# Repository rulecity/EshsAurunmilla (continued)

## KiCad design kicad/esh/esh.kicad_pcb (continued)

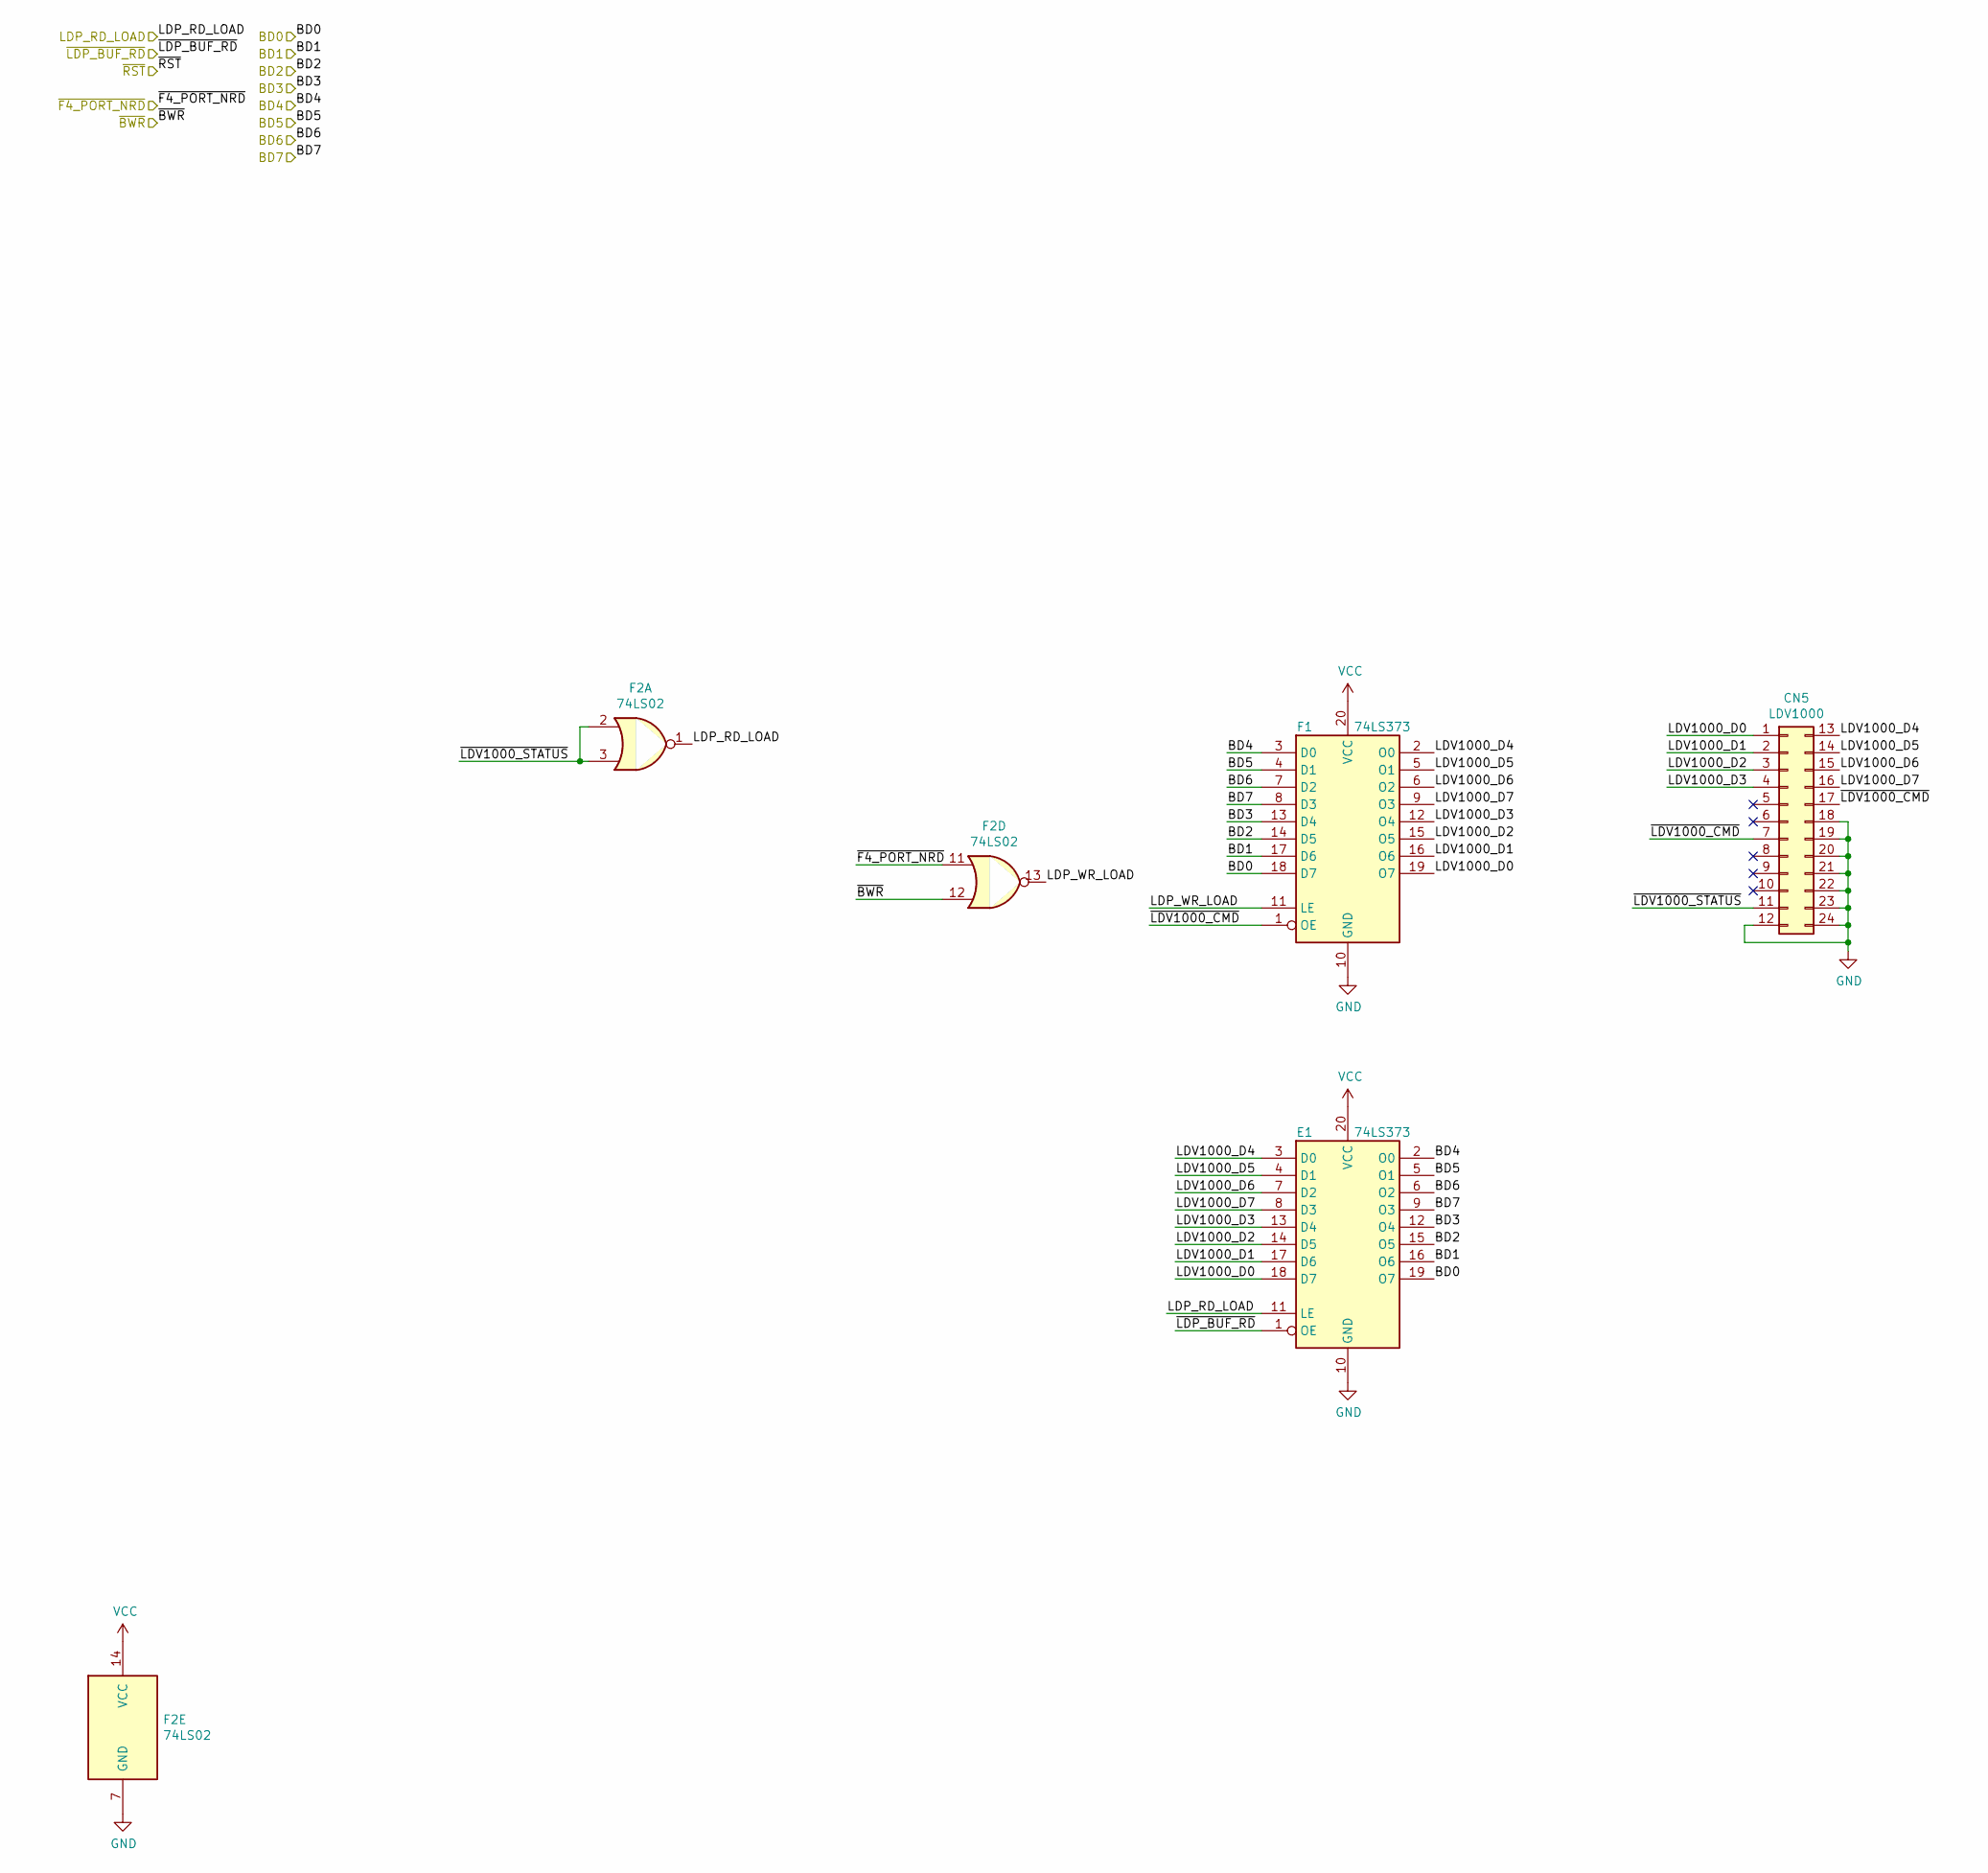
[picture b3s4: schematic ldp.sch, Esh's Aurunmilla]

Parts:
CN5: LDV1000; Esh_LDV1000
E1: 74LS373; DIP-20_W7.62mm_Socket
F1: 74LS373; DIP-20_W7.62mm_Socket
F2: 74LS02; DIP-14_W7.62mm_Socket

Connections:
/BD0: E1.19 (O7), F1.18 (D7); also elsewhere on the board
/BD1: E1.16 (O6), F1.17 (D6); also elsewhere on the board
/BD2: E1.15 (O5), F1.14 (D5); also elsewhere on the board
/BD3: E1.12 (O4), F1.13 (D4); also elsewhere on the board
/BD4: E1.2 (O0), F1.3 (D0); also elsewhere on the board
/BD5: E1.5 (O1), F1.4 (D1); also elsewhere on the board
/BD6: E1.6 (O2), F1.7 (D2); also elsewhere on the board
/BD7: E1.9 (O3), F1.8 (D3); also elsewhere on the board
/LDP_RD_LOAD: E1.11 (LE), F2.1; also elsewhere on the board
/ldp/LDP_WR_LOAD: F1.11 (LE), F2.13
/ldp/LDV1000_D0: CN5.1, E1.18 (D7), F1.19 (O7)
/ldp/LDV1000_D1: CN5.2, E1.17 (D6), F1.16 (O6)
/ldp/LDV1000_D2: CN5.3, E1.14 (D5), F1.15 (O5)
/ldp/LDV1000_D3: CN5.4, E1.13 (D4), F1.12 (O4)
/ldp/LDV1000_D4: CN5.13, E1.3 (D0), F1.2 (O0)
/ldp/LDV1000_D5: CN5.14, E1.4 (D1), F1.5 (O1)
/ldp/LDV1000_D6: CN5.15, E1.7 (D2), F1.6 (O2)
/ldp/LDV1000_D7: CN5.16, E1.8 (D3), F1.9 (O3)
/ldp/~LDV1000_CMD: CN5.7, CN5.17, F1.1 (OE)
/ldp/~LDV1000_STATUS: CN5.11, F2.2, F2.3
/~BWR: F2.12; also elsewhere on the board
/~F4_PORT_NRD: F2.11; also elsewhere on the board
/~LDP_BUF_RD: E1.1 (OE); also elsewhere on the board
GND: CN5.12, CN5.18, CN5.19, CN5.20, CN5.21, CN5.22, CN5.23, CN5.24, E1.10 (GND), F1.10 (GND), F2.7 (GND); also elsewhere on the board
VCC: E1.20 (VCC), F1.20 (VCC), F2.14 (VCC); also elsewhere on the board

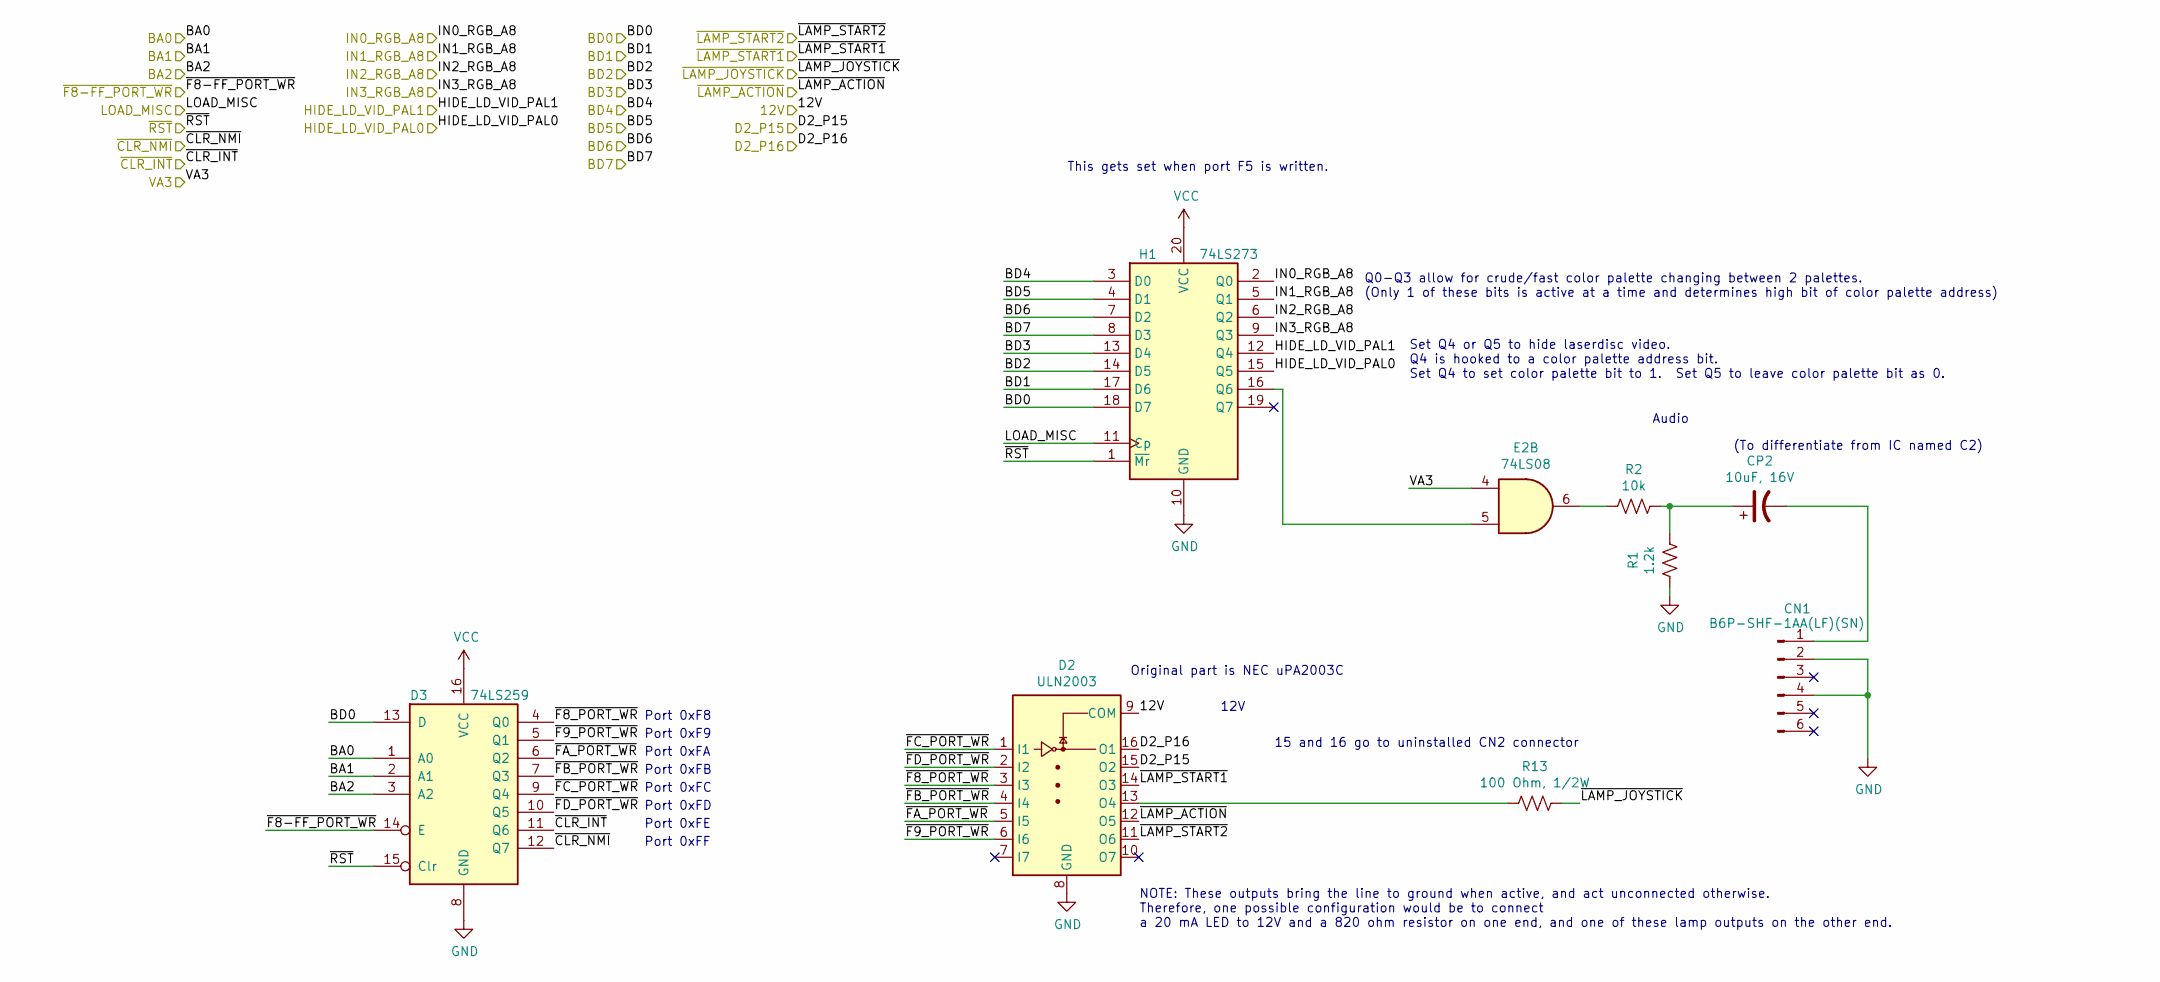
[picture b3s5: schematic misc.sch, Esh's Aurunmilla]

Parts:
CN1: B6P-SHF-1AA(LF)(SN); PinHeader_1x06_P2.54mm_Vertical
CP2: 10uF, 16V; CP_Radial_D5.0mm_P2.50mm
D2: ULN2003; DIP-16_W7.62mm_Socket
D3: 74LS259; DIP-16_W7.62mm_Socket
E2: 74LS08; DIP-14_W7.62mm_Socket
H1: 74LS273; DIP-20_W7.62mm_Socket
R1: 1.2k; R_Axial_DIN0207_L6.3mm_D2.5mm_P10.16mm_Horizontal
R2: 10k; R_Axial_DIN0207_L6.3mm_D2.5mm_P10.16mm_Horizontal
R13: 100 Ohm, 1/2W; R_Axial_DIN0207_L6.3mm_D2.5mm_P10.16mm_Horizontal

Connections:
/12V: D2.9 (COM); also elsewhere on the board
/BA0: D3.1 (A0); also elsewhere on the board
/BA1: D3.2 (A1); also elsewhere on the board
/BA2: D3.3 (A2); also elsewhere on the board
/BD0: D3.13 (D), H1.18 (D7); also elsewhere on the board
/BD1: H1.17 (D6); also elsewhere on the board
/BD2: H1.14 (D5); also elsewhere on the board
/BD3: H1.13 (D4); also elsewhere on the board
/BD4: H1.3 (D0); also elsewhere on the board
/BD5: H1.4 (D1); also elsewhere on the board
/BD6: H1.7 (D2); also elsewhere on the board
/BD7: H1.8 (D3); also elsewhere on the board
/D2_P15: D2.15 (O2); also elsewhere on the board
/D2_P16: D2.16 (O1); also elsewhere on the board
/HIDE_LD_VID_PAL0: H1.15 (Q5); also elsewhere on the board
/HIDE_LD_VID_PAL1: H1.12 (Q4); also elsewhere on the board
/IN0_RGB_A8: H1.2 (Q0); also elsewhere on the board
/IN1_RGB_A8: H1.5 (Q1); also elsewhere on the board
/IN2_RGB_A8: H1.6 (Q2); also elsewhere on the board
/IN3_RGB_A8: H1.9 (Q3); also elsewhere on the board
/LOAD_MISC: H1.11 (Cp); also elsewhere on the board
/VA3: E2.4; also elsewhere on the board
/misc/~F8_PORT_WR: D2.3 (I3), D3.4 (Q0)
/misc/~F9_PORT_WR: D2.6 (I6), D3.5 (Q1)
/misc/~FA_PORT_WR: D2.5 (I5), D3.6 (Q2)
/misc/~FB_PORT_WR: D2.4 (I4), D3.7 (Q3)
/misc/~FC_PORT_WR: D2.1 (I1), D3.9 (Q4)
/misc/~FD_PORT_WR: D2.2 (I2), D3.10 (Q5)
/~CLR_INT: D3.11 (Q6); also elsewhere on the board
/~CLR_NMI: D3.12 (Q7); also elsewhere on the board
/~F8-FF_PORT_WR: D3.14 (E); also elsewhere on the board
/~LAMP_ACTION: D2.12 (O5); also elsewhere on the board
/~LAMP_JOYSTICK: R13.1; also elsewhere on the board
/~LAMP_START1: D2.14 (O3); also elsewhere on the board
/~LAMP_START2: D2.11 (O6); also elsewhere on the board
/~RST: D3.15 (Clr), H1.1 (~Mr); also elsewhere on the board
GND: CN1.2, CN1.4, D2.8 (GND), D3.8 (GND), H1.10 (GND), R1.2; also elsewhere on the board
unnamed: CN1.1, CP2.2
unnamed: CP2.1, R1.1, R2.1
unnamed: D2.13 (O4), R13.2
unnamed: E2.5, H1.16 (Q6)
unnamed: E2.6, R2.2
VCC: D3.16 (VCC), H1.20 (VCC); also elsewhere on the board

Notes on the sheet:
Port 0xFF
Port 0xFE
Port 0xF8
Port 0xF9
Port 0xFA
Port 0xFB
Port 0xFC
Port 0xFD
15 and 16 go to uninstalled CN2 connector
Original part is NEC uPA2003C
12V
This gets set when port F5 is written.
Audio
(To differentiate from IC named C2)
Set Q4 or Q5 to hide laserdisc video. Q4 is hooked to a color palette address bit. Set Q4 to set color palette bit to 1. Set Q5 to leave color palette bit as 0.
Q0-Q3 allow for crude/fast color palette changing between 2 palettes. (Only 1 of these bits is active at a time and determines high bit of color palette address)
NOTE: These outputs bring the line to ground when active, and act unconnected otherwise. Therefore, one possible configuration would be to connect a 20 mA LED to 12V and a 820 ohm resistor on one end, and one of these lamp outputs on the other end.

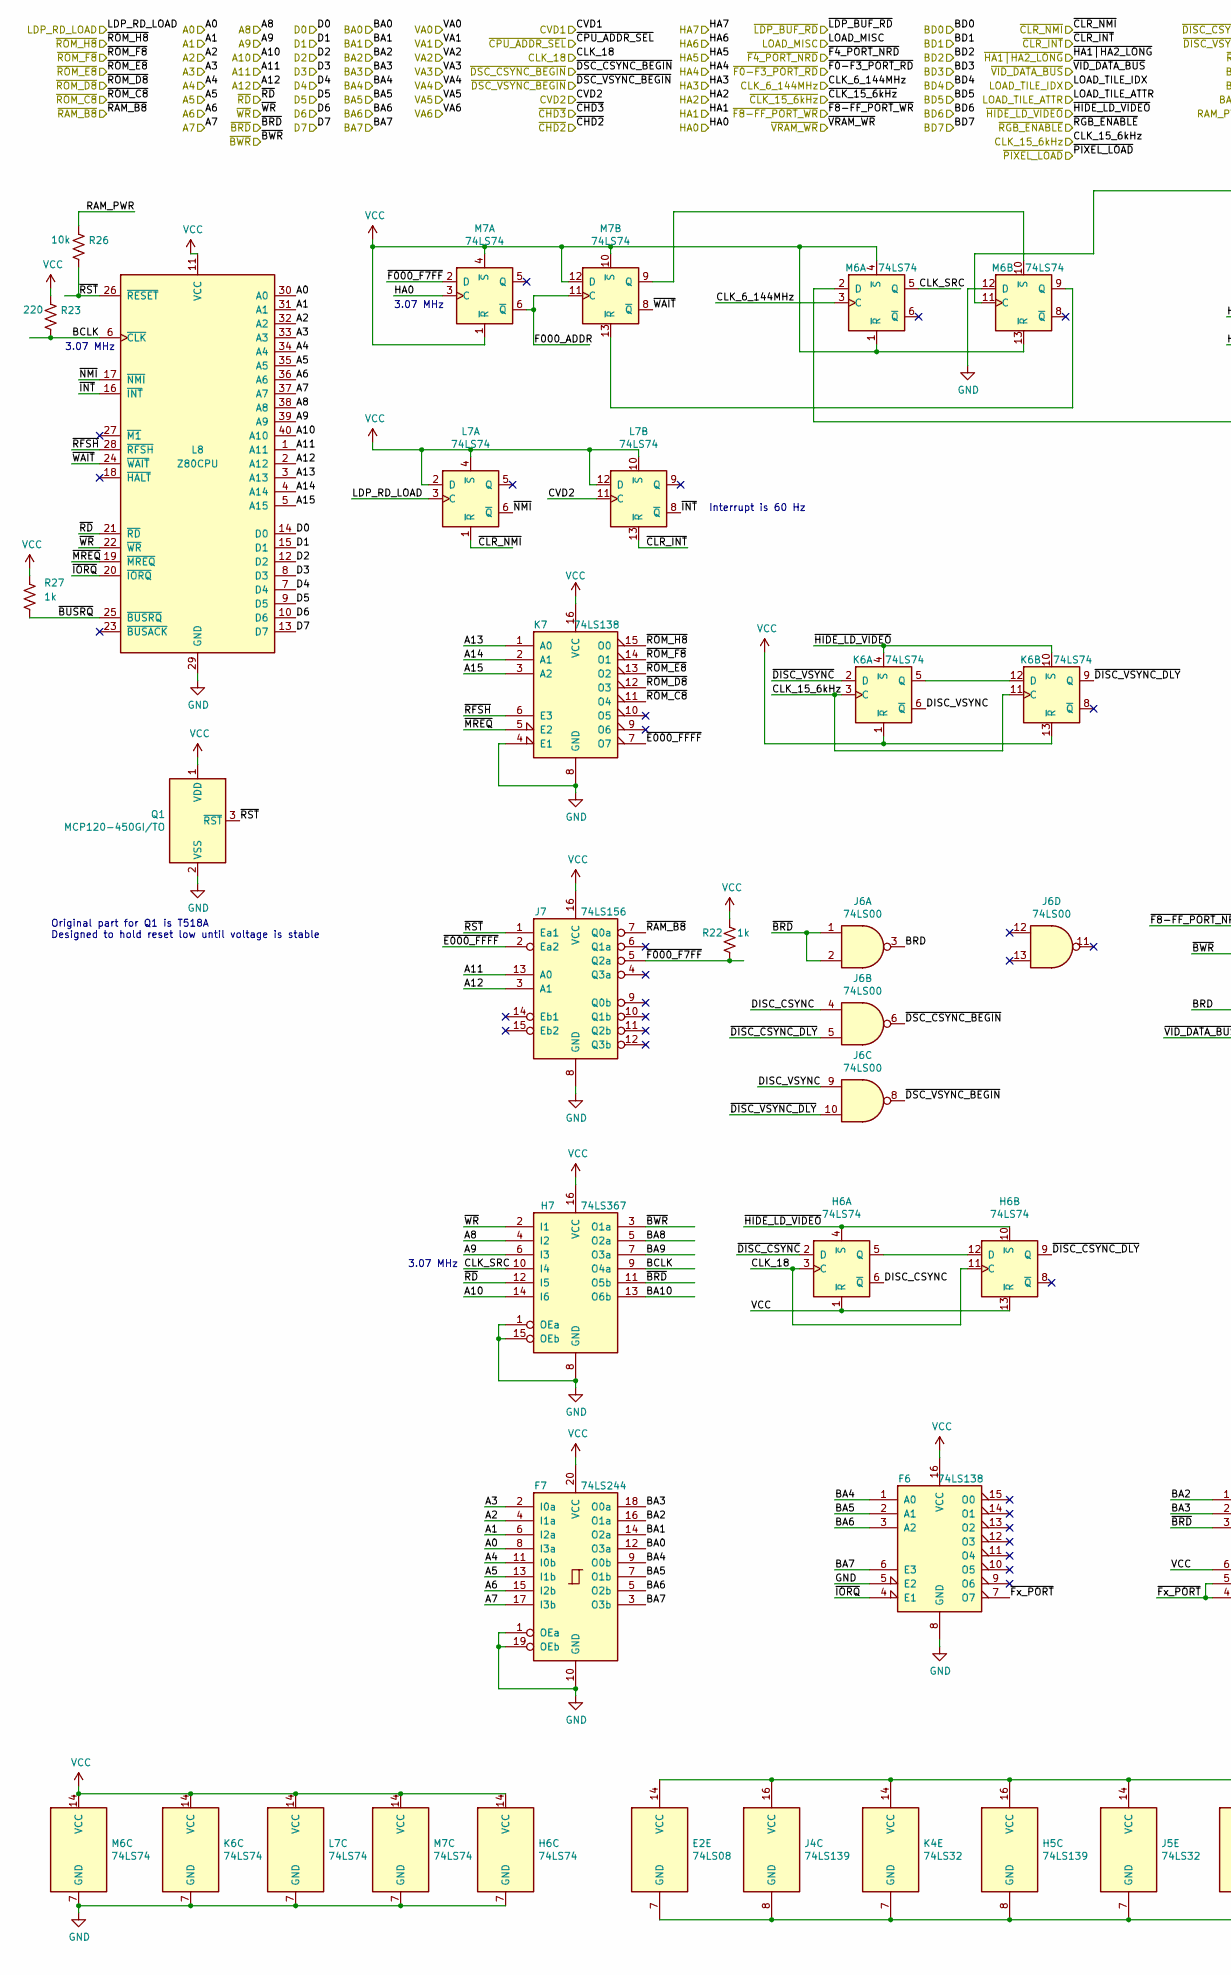
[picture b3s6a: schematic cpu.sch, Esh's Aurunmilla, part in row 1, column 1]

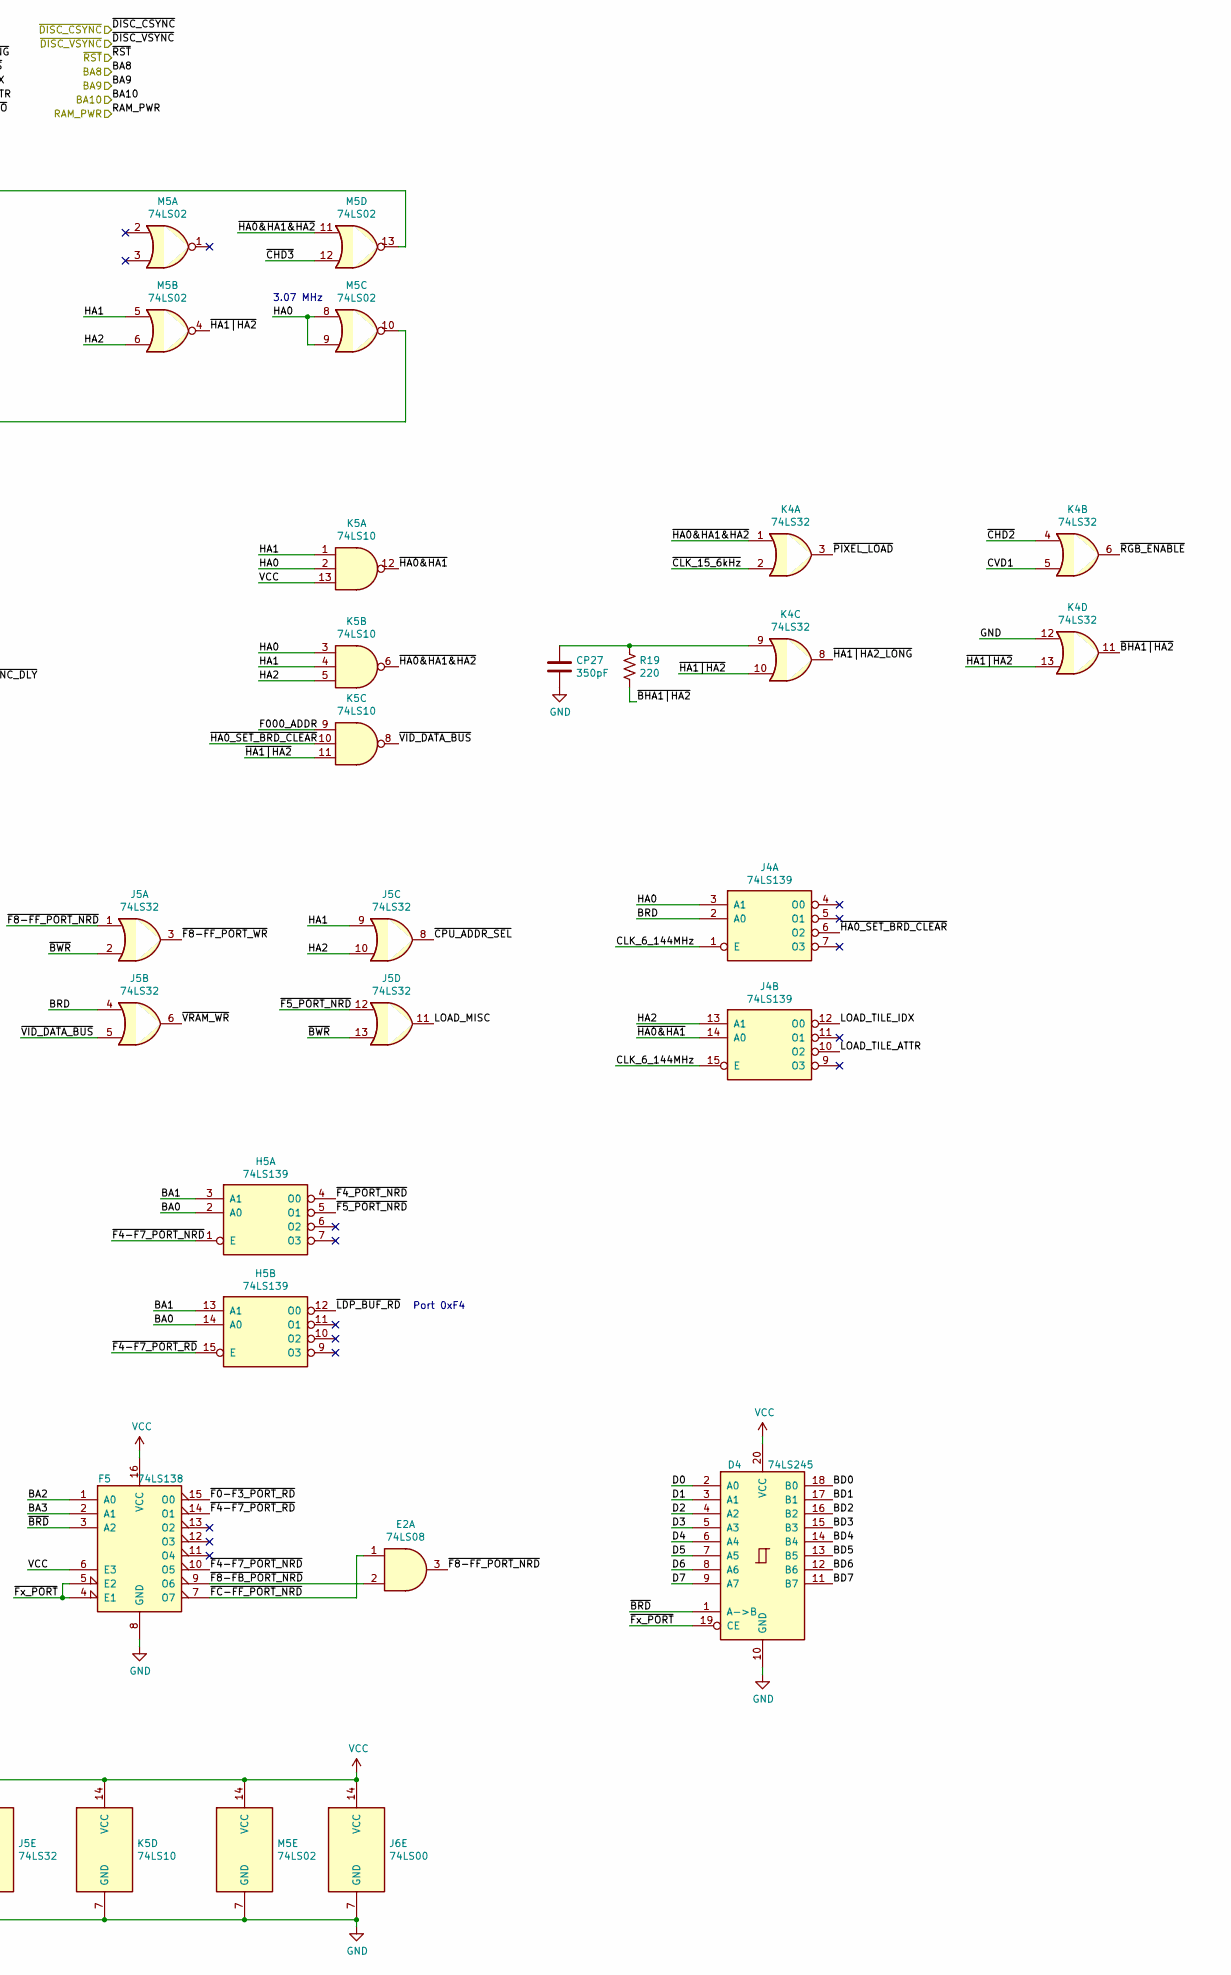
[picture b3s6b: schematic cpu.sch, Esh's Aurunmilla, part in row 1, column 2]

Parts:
CP27: 350pF; R_Axial_DIN0204_L3.6mm_D1.6mm_P5.08mm_Horizontal
D4: 74LS245; DIP-20_W7.62mm_Socket
E2: 74LS08; DIP-14_W7.62mm_Socket
F5, F6: 74LS138; DIP-16_W7.62mm_Socket
F7: 74LS244; DIP-20_W7.62mm_Socket
H5: 74LS139; DIP-16_W7.62mm_Socket
H6: 74LS74; DIP-14_W7.62mm_Socket
H7: 74LS367; DIP-16_W7.62mm_Socket
J4: 74LS139; DIP-16_W7.62mm_Socket
J5: 74LS32; DIP-14_W7.62mm_Socket
J6: 74LS00; DIP-14_W7.62mm_Socket
J7: 74LS156; DIP-16_W7.62mm_Socket
K4: 74LS32; DIP-14_W7.62mm_Socket
K5: 74LS10; DIP-14_W7.62mm_Socket
K6: 74LS74; DIP-14_W7.62mm_Socket
K7: 74LS138; DIP-16_W7.62mm_Socket
L7: 74LS74; DIP-14_W7.62mm_Socket
L8: Z80CPU; DIP-40_W15.24mm_Socket
M5: 74LS02; DIP-14_W7.62mm_Socket
M6, M7: 74LS74; DIP-14_W7.62mm_Socket
Q1: MCP120-450GI/TO; TO-92_Inline
R19, R23: 220; R_Axial_DIN0207_L6.3mm_D2.5mm_P10.16mm_Horizontal
R22, R27: 1k; R_Axial_DIN0207_L6.3mm_D2.5mm_P10.16mm_Horizontal
R26: 10k; R_Axial_DIN0207_L6.3mm_D2.5mm_P10.16mm_Horizontal

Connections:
/A0: F7.8 (I3a), L8.30 (A0); also elsewhere on the board
/A1: F7.6 (I2a), L8.31 (A1); also elsewhere on the board
/A2: F7.4 (I1a), L8.32 (A2); also elsewhere on the board
/A3: F7.2 (I0a), L8.33 (A3); also elsewhere on the board
/A4: F7.11 (I0b), L8.34 (A4); also elsewhere on the board
/A5: F7.13 (I1b), L8.35 (A5); also elsewhere on the board
/A6: F7.15 (I2b), L8.36 (A6); also elsewhere on the board
/A7: F7.17 (I3b), L8.37 (A7); also elsewhere on the board
/A8: H7.4 (I2), L8.38 (A8); also elsewhere on the board
/A9: H7.6 (I3), L8.39 (A9); also elsewhere on the board
/A10: H7.14 (I6), L8.40 (A10); also elsewhere on the board
/A11: J7.13 (A0), L8.1 (A11); also elsewhere on the board
/A12: J7.3 (A1), L8.2 (A12); also elsewhere on the board
/BA0: F7.12 (O3a), H5.2 (A0), H5.14 (A0); also elsewhere on the board
/BA1: F7.14 (O2a), H5.3 (A1), H5.13 (A1); also elsewhere on the board
/BA2: F5.1 (A0), F7.16 (O1a); also elsewhere on the board
/BA3: F5.2 (A1), F7.18 (O0a); also elsewhere on the board
/BA4: F6.1 (A0), F7.9 (O0b); also elsewhere on the board
/BA5: F6.2 (A1), F7.7 (O1b); also elsewhere on the board
/BA6: F6.3 (A2), F7.5 (O2b); also elsewhere on the board
/BA7: F6.6 (E3), F7.3 (O3b); also elsewhere on the board
/BA8: H7.5 (O2a); also elsewhere on the board
/BA9: H7.7 (O3a); also elsewhere on the board
/BA10: H7.13 (O6b); also elsewhere on the board
/BD0: D4.18 (B0); also elsewhere on the board
/BD1: D4.17 (B1); also elsewhere on the board
/BD2: D4.16 (B2); also elsewhere on the board
/BD3: D4.15 (B3); also elsewhere on the board
/BD4: D4.14 (B4); also elsewhere on the board
/BD5: D4.13 (B5); also elsewhere on the board
/BD6: D4.12 (B6); also elsewhere on the board
/BD7: D4.11 (B7); also elsewhere on the board
/CLK_6_144MHz: J4.1 (E), J4.15 (E), M6.3 (C); also elsewhere on the board
/CLK_15_6kHz: K6.3 (C), K6.11 (C); also elsewhere on the board
/CLK_18_432MHz: H6.3 (C), H6.11 (C); also elsewhere on the board
/CVD1: K4.5; also elsewhere on the board
/CVD2: L7.11 (C); also elsewhere on the board
/D0: D4.2 (A0), L8.14 (D0); also elsewhere on the board
/D1: D4.3 (A1), L8.15 (D1); also elsewhere on the board
/D2: D4.4 (A2), L8.12 (D2); also elsewhere on the board
/D3: D4.5 (A3), L8.8 (D3); also elsewhere on the board
/D4: D4.6 (A4), L8.7 (D4); also elsewhere on the board
/D5: D4.7 (A5), L8.9 (D5); also elsewhere on the board
/D6: D4.8 (A6), L8.10 (D6); also elsewhere on the board
/D7: D4.9 (A7), L8.13 (D7); also elsewhere on the board
/HA0: J4.3 (A1), K5.2, K5.3, M5.8, M5.9, M7.3 (C); also elsewhere on the board
/HA1: J5.9, K5.1, K5.4, M5.5; also elsewhere on the board
/HA2: J4.13 (A1), J5.10, K5.5, M5.6; also elsewhere on the board
/LDP_RD_LOAD: L7.3 (C); also elsewhere on the board
/LOAD_MISC: J5.11; also elsewhere on the board
/LOAD_TILE_ATTR: J4.10 (O2); also elsewhere on the board
/LOAD_TILE_IDX: J4.12 (O0); also elsewhere on the board
/RAM_PWR: R26.1; also elsewhere on the board
/cpu/A13: K7.1 (A0), L8.3 (A13)
/cpu/A14: K7.2 (A1), L8.4 (A14)
/cpu/A15: K7.3 (A2), L8.5 (A15)
/cpu/BCLK: H7.9 (O4a), L8.6 (~CLK~), R23.2
/cpu/BRD: J4.2 (A0), J5.4, J6.3
/cpu/CLK_SRC: H7.10 (I4), M6.5 (Q)
/cpu/DISC_CSYNC: H6.6 (~Q), J6.4
/cpu/DISC_VSYNC: J6.9, K6.6 (~Q)
/cpu/F000_ADDR: K5.9, M7.6 (~Q), M7.11 (C)
/cpu/~BHA1|HA2: K4.11, R19.2
/cpu/~BUSRQ: L8.25 (~BUSRQ~), R27.2
/cpu/~DISC_CSYNC_DLY: H6.9 (Q), J6.5
/cpu/~DISC_VSYNC_DLY: J6.10, K6.9 (Q)
/cpu/~E000_FFFF: J7.2 (Ea2), K7.7 (O7)
/cpu/~F000_F7FF: J7.5 (Q2a), M7.2 (D), R22.2
/cpu/~F4-F7_PORT_NRD: F5.10 (O5), H5.1 (E)
/cpu/~F4-F7_PORT_RD: F5.14 (O1), H5.15 (E)
/cpu/~F5_PORT_NRD: H5.5 (O1), J5.12
/cpu/~F8-FB_PORT_NRD: E2.2, F5.9 (O6)
/cpu/~F8-FF_PORT_NRD: E2.3, J5.1
/cpu/~FC-FF_PORT_NRD: E2.1, F5.7 (O7)
/cpu/~Fx_PORT: D4.19 (CE), F5.4 (E1), F5.5 (E2), F6.7 (O7)
/cpu/~HA0&HA1: J4.14 (A0), K5.12
/cpu/~HA0&HA1&HA2: K4.1, K5.6, M5.11
/cpu/~HA0_SET_BRD_CLEAR: J4.6 (O2), K5.10
/cpu/~HA1|HA2: K4.10, K4.13, K5.11, M5.4
/cpu/~INT: L7.8 (~Q), L8.16 (~INT~)
/cpu/~IORQ: F6.4 (E1), L8.20 (~IORQ~)
/cpu/~MREQ: K7.5 (E2), L8.19 (~MREQ~)
/cpu/~NMI: L7.6 (~Q), L8.17 (~NMI~)
/cpu/~RFSH: K7.6 (E3), L8.28 (~RFSH~)
/cpu/~WAIT: L8.24 (~WAIT~), M7.8 (~Q)
/~BRD: D4.1 (A->B), F5.3 (A2), H7.11 (O5b), J6.1, J6.2; also elsewhere on the board
/~BWR: H7.3 (O1a), J5.2, J5.13; also elsewhere on the board
/~CHD2: K4.4; also elsewhere on the board
/~CHD3: M5.12; also elsewhere on the board
/~CLK_15_6kHz: K4.2; also elsewhere on the board
/~CLR_INT: L7.13 (~R); also elsewhere on the board
/~CLR_NMI: L7.1 (~R); also elsewhere on the board
/~CPU_ADDR_SEL: J5.8; also elsewhere on the board
/~DISC_CSYNC: H6.2 (D); also elsewhere on the board
/~DISC_VSYNC: K6.2 (D); also elsewhere on the board
/~DSC_CSYNC_BEGIN: J6.6; also elsewhere on the board
/~DSC_VSYNC_BEGIN: J6.8; also elsewhere on the board
/~F0-F3_PORT_RD: F5.15 (O0); also elsewhere on the board
/~F4_PORT_NRD: H5.4 (O0); also elsewhere on the board
/~F8-FF_PORT_WR: J5.3; also elsewhere on the board
/~HA1|HA2_LONG: K4.8; also elsewhere on the board
/~HIDE_LD_VIDEO: H6.4 (~S), H6.10 (~S), K6.4 (~S), K6.10 (~S); also elsewhere on the board
/~LDP_BUF_RD: H5.12 (O0); also elsewhere on the board
/~PIXEL_LOAD: K4.3; also elsewhere on the board
/~RAM_B8: J7.7 (Q0a); also elsewhere on the board
/~RD: H7.12 (I5), L8.21 (~RD~); also elsewhere on the board
/~RGB_ENABLE: K4.6; also elsewhere on the board
/~ROM_C8: K7.11 (O4); also elsewhere on the board
/~ROM_D8: K7.12 (O3); also elsewhere on the board
/~ROM_E8: K7.13 (O2); also elsewhere on the board
/~ROM_F8: K7.14 (O1); also elsewhere on the board
/~ROM_H8: K7.15 (O0); also elsewhere on the board
/~RST: J7.1 (Ea1), L8.26 (~RESET~), Q1.3 (~RST), R26.2; also elsewhere on the board
/~VID_DATA_BUS: J5.5, K5.8; also elsewhere on the board
/~VRAM_WR: J5.6; also elsewhere on the board
/~WR: H7.2 (I1), L8.22 (~WR~); also elsewhere on the board
GND: CP27.2, D4.10 (GND), E2.7 (GND), F5.8 (GND), F6.5 (E2), F6.8 (GND), F7.1 (OEa), F7.10 (GND), F7.19 (OEb), H5.8 (GND), H6.7 (GND), H7.1 (OEa), H7.8 (GND), H7.15 (OEb), J4.8 (GND), J5.7 (GND), J6.7 (GND), J7.8 (GND), K4.7 (GND), K4.12, K5.7 (GND), K6.7 (GND), K7.4 (E1), K7.8 (GND), L7.7 (GND), L8.29 (GND), M5.7 (GND), M6.7 (GND), M6.12 (D), M7.7 (GND), Q1.2 (VSS); also elsewhere on the board
unnamed: CP27.1, K4.9, R19.1
unnamed: H6.5 (Q), H6.12 (D)
unnamed: K6.5 (Q), K6.12 (D)
unnamed: M5.10, M6.2 (D)
unnamed: M5.13, M6.11 (C)
unnamed: M6.9 (Q), M7.13 (~R)
unnamed: M6.10 (~S), M7.9 (Q)
VCC: D4.20 (VCC), E2.14 (VCC), F5.6 (E3), F5.16 (VCC), F6.16 (VCC), F7.20 (VCC), H5.16 (VCC), H6.1 (~R), H6.13 (~R), H6.14 (VCC), H7.16 (VCC), J4.16 (VCC), J5.14 (VCC), J6.14 (VCC), J7.16 (VCC), K4.14 (VCC), K5.13, K5.14 (VCC), K6.1 (~R), K6.13 (~R), K6.14 (VCC), K7.16 (VCC), L7.2 (D), L7.4 (~S), L7.10 (~S), L7.12 (D), L7.14 (VCC), L8.11 (VCC), M5.14 (VCC), M6.1 (~R), M6.4 (~S), M6.13 (~R), M6.14 (VCC), M7.1 (~R), M7.4 (~S), M7.10 (~S), M7.12 (D), M7.14 (VCC), Q1.1 (VDD), R22.1, R23.1, R27.1; also elsewhere on the board

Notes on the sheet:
Original part for Q1 is T518A Designed to hold reset low until voltage is stable
3.07 MHz
Port 0xF4
Interrupt is 60 Hz
